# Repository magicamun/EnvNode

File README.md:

# EnvNode

EnvNode is an source-available ESP32-based embedded platform for reliable environmental measurements and seamless integration into modern home automation systems.

WeatherStation is the first reference application built on the reusable EnvNode platform.

The classic ESP32 firmware keeps Arduino-ESP32 2.x and RainDetector, with UDP
logging to rsyslog instead of SD storage. SD and SX1262 runtime support belong
to the later S3 hardware/build profile. See the [classic ESP32 scope](docs/ClassicEsp32Scope.md)
and [logging validation](docs/UdpLoggingValidation.md) for current limits and measurements.

The project intentionally separates **measurement** from **interpretation**.

The firmware is responsible for acquiring reliable physical Measurements and publishing them to external systems.

Higher-level concepts such as weather interpretation, historical aggregation, evapotranspiration (ETo), irrigation logic and visualization intentionally remain outside the firmware.

EnvNode is developed as a complete source-available product including:

- firmware
- hardware (KiCad)
- documentation
- development tooling

The goal is not to build another weather dashboard.

The goal is to build a reliable measurement platform.

---

# Vision

EnvNode provides an open, transparent and extensible weather sensor platform for Home Assistant and other home automation systems.

The ESP32 acts as a dedicated measurement node.

It acquires physical sensor data, performs only the hardware-related processing required to obtain reliable Measurements and publishes them via MQTT.

The firmware intentionally remains deterministic, maintainable and independent from weather-specific interpretation.

This allows higher software layers to evolve independently while keeping the embedded firmware simple and robust.

---

# Why another weather station?

The project originated from practical experience with an existing DIY weather station.

Although the hardware proved to be reliable, several software aspects became increasingly problematic:

- closed-source firmware
- undocumented algorithms
- incorrect sunshine duration calculation
- embedded rain aggregation
- limited extensibility
- unclear separation between measurement and interpretation

Rather than replacing individual algorithms, the firmware was redesigned from first principles around a small number of architectural rules.

---

# Core Philosophy

The EnvNode project follows one simple principle:

> Measure first.
>
> Interpret later.

The firmware exists to acquire reliable Measurements.

Interpretation belongs to external systems.

---

# Project Goals

- source-available firmware with a commercial exploitation reservation
- available hardware design sources (KiCad)
- MQTT-based integration
- browser-based configuration
- OTA firmware updates
- modular architecture
- high-quality Measurements
- deterministic firmware behaviour
- long-term maintainability
- simulation support
- comprehensive documentation
- hardware independence

---

# Design Principles

The project follows a small number of architectural principles.

### Measure, don't interpret

The firmware measures physical reality.

Interpretation belongs outside the Device.

---

### One technical responsibility per service

Each infrastructure service owns exactly one technical responsibility.

Examples include:

- Configuration
- WiFi
- Time
- MQTT

---

### Sensors produce Measurements

Sensors do not publish MQTT.

Sensors do not interpret weather.

Sensors produce Measurements.

### Controllers coordinate Actuators through capabilities

Controllers implement cooperative local behavior and address configured Actuators by `ActuatorId` and capability. They do not manipulate GPIO or use MQTT as an internal control path.

---

### Configuration has one authoritative owner

Configuration exists exactly once inside the runtime.

Every subsystem uses the same Configuration.

---

### Simulation is part of the architecture

Simulated and physical Sensors follow the same processing pipeline.

Replacing a simulated Sensor with a physical implementation must not require architectural changes.

---

### Observable behaviour

Whenever practical, internal decisions should be visible through:

- diagnostics
- logging
- MQTT status

The firmware should never behave like a black box.

---

### Deterministic firmware

The firmware intentionally avoids executing complex weather models.

Embedded software should remain predictable and responsive.

---

### Hardware independence

Application logic depends on abstract Sensor behaviour rather than concrete hardware implementations.

Replacing a Sensor should require only a new driver.

---

# Current Status

Implemented

- ESP32 PlatformIO project
- persistent configuration
- browser-based provisioning
- WiFi connectivity
- automatic WiFi reconnect
- setup access point
- configurable hostname
- SNTP time synchronization
- configurable timezone
- MQTT connectivity
- authenticated MQTT client
- factory reset and OTA firmware update
- typed Measurement pipeline and MQTT publication
- fixed Sensor slots, physical/simulated implementations and live runtime composition
- Sensor Home Assistant discovery
- optional GeoPosition and actual sensor altitude, persisted with backup/restore
- separate sea-level pressure with local temperature selection, freshness checking,
  explicit quality and fallback diagnostics (firmware 0.6.0)
- EEPROM-backed Board Identity, boot-time profile resolution and development fallback
- Board Identity diagnostics and confirmed Web provisioning with readback verification
- independent Module Identity discovery for both slots, immutable module profiles and
  board/slot compatibility diagnostics without automatic driver activation
- fixed Actuator slots and unified hardware validation
- OnOff capability and GPIO On/Off Actuator
- Level capability and GPIO PWM Actuator
- live Actuator runtime rebuild
- Web and MQTT Actuator configuration/control
- fixed Controller slots and BlinkController
- ThresholdController with typed Measurement input, hysteresis and monotonic freshness
- cooperative Controller runtime and live rebuild
- Web and MQTT Controller configuration, status and Start/Stop
- persistent MQTT Blink/Threshold parameter commands and retained parameter state
- retained external Actuator and Controller descriptions
- exclusive enabled-Controller ownership of Actuator targets
- physically verified Sensor -> Measurement -> Controller -> Actuator operation

Current hardware-validation focus

- provision and boot from the Board Identity EEPROM on a physical Mainboard revision 0.3
- complete the Revision 0.3 article list and assembly data
- assemble and bring up the AnalogHydroPressure module, including its local 5 V to 24 V supply
- integrate and calibrate the ADS1115-based 4–20 mA pressure input on real hardware
- operate at least the Rain Detector heater path before releasing Revision 0.3 for production

Deliberately future

- additional Actuator capabilities beyond OnOff and Level, and additional typed Controller implementations
- multi-input, Boolean/contact and event-driven Controllers
- richer manual-versus-Controller arbitration
- Controller and generic Actuator Home Assistant discovery
- a dedicated provisioning station for preparing Mainboards, Modules, and other supported boards

---

# Documentation

Project documentation is intentionally separated by responsibility.

| Document | Purpose |
|----------|---------|
| README.md | Project overview |
| DomainModel.md | Functional domain concepts |
| TechnicalArchitecture.md | Technical architecture |
| ActuatorModel.md | Actuator capabilities and Controller interaction |
| MQTT.md | Current MQTT protocol boundaries and topics |
| Configuration.md | Configuration backup, restore and NVS persistence |
| [SeaLevelPressure.md](docs/SeaLevelPressure.md) | GeoPosition, local temperature input and derived sea-level pressure |
| Hardware.md | Hardware entry point, module templates, and implemented boards |
| [PRODUCT_ASSET_CONTRACT.md](docs/PRODUCT_ASSET_CONTRACT.md) | Reproducible PCB and webshop image requirements |
| ADRs | Architectural decisions |

---

# Non Goals

EnvNode intentionally does not:

- perform weather forecasting
- calculate evapotranspiration (ETo)
- calculate sunshine duration
- aggregate historical weather data
- store long-term measurements
- replace Home Assistant

These responsibilities belong to higher software layers.

---

# Project Status

The Sensor, Actuator and Controller architecture is implemented and physically verified. Current open work concerns further capabilities, Controller implementations and external self-description rather than replacing these runtime boundaries.

# License and permitted use

EnvNode-owned materials are provided under the [EnvNode Use and Redistribution
License, version 1.0](LICENSE). Private and internal business use, modifications,
free redistribution, and paid fabrication or maintenance for the user's own use
are permitted. Commercial product sales, licensing, rental, and standalone paid
software hosting require separate permission. Third-party materials retain their
respective licenses. This is a custom source-available license, not an
OSI-approved open-source license. The German license text is authoritative.

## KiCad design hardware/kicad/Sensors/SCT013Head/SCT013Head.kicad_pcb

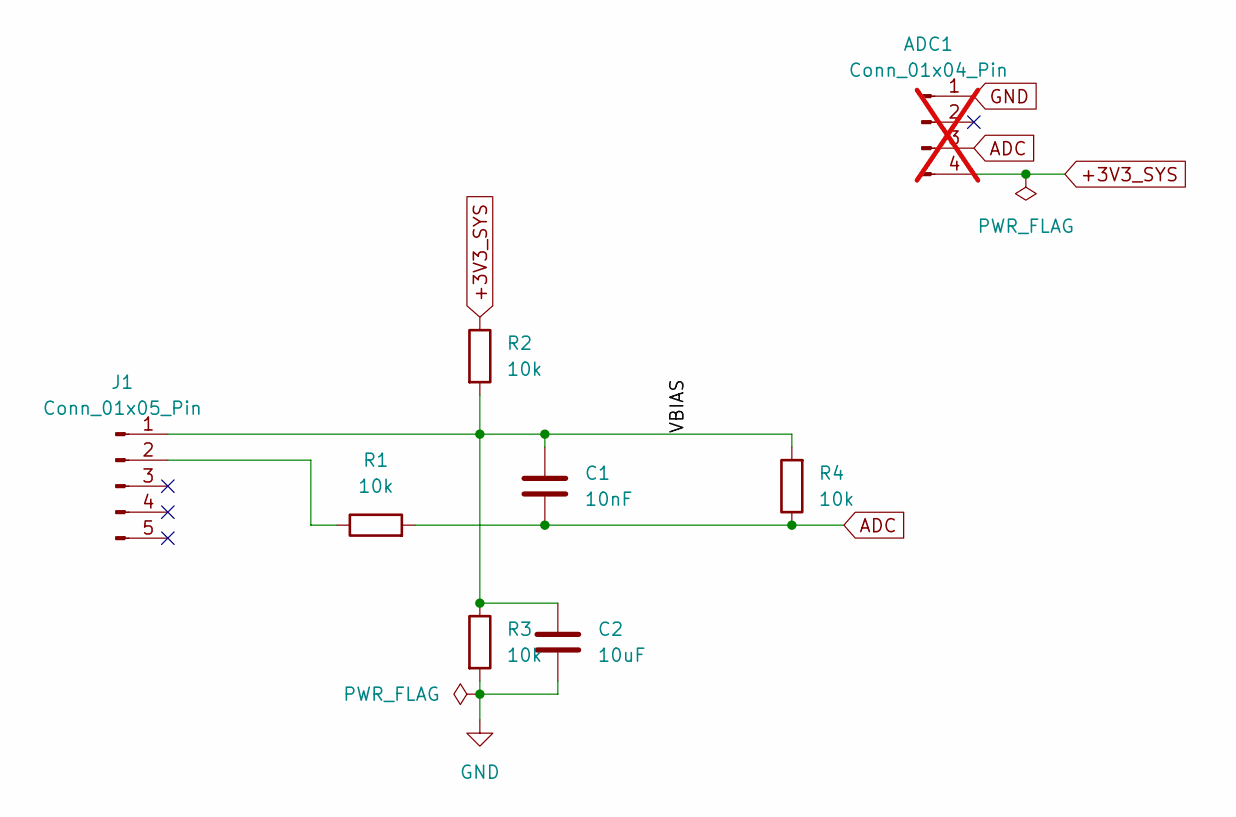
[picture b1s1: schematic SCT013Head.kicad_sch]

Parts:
ADC1: Conn_01x04_Pin; PinHeader_1x04_P2.54mm_Vertical; not fitted
C1: 10nF; C_1206_3216Metric_Pad1.33x1.80mm_HandSolder
C2: 10uF; C_1206_3216Metric_Pad1.33x1.80mm_HandSolder
J1: Conn_01x05_Pin; Jack_3.5mm_Lumberg_1503_09_Horizontal
R1, R2, R3, R4: 10k; R_1206_3216Metric_Pad1.30x1.75mm_HandSolder

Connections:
+3V3_SYS: ADC1.4, R2.1
/VBIAS: C1.1, C2.1, J1.1, R2.2, R3.1, R4.2
ADC: ADC1.3, C1.2, R1.2, R4.1
GND: ADC1.1, C2.2, R3.2
unnamed: J1.2, R1.1

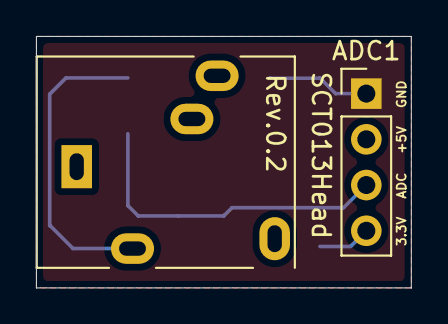
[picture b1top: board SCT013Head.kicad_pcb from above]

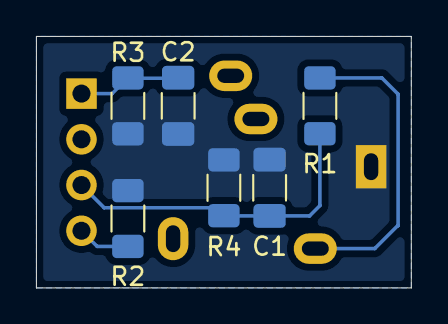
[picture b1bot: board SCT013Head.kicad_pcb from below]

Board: 2 copper layers, 20.8 x 14.0 mm, 8 parts (6 on the bottom side), 5 nets.

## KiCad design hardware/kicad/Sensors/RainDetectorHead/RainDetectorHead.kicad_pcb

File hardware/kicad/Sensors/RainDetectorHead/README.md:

# EnvNode RainDetector Head — Revision 0.2

## Current mechanical revision - 2026-10-21

PCB **ENP-00139**, revision **0.2**, paired with RainDetectorController **0.4**.
The outline is **62.12 x 54.52 mm** (Edge.Cuts centerline), enlarged for the
housing seal; mounting holes moved with the outline. The active C1 detector
geometry, J1/J2 positions/orientations and PCB pad-net assignments are unchanged
relative to the previous committed PCB. No electrical or firmware change follows
from this mechanical revision. The head C1 footprint identifier is
`RainDetector_Interdigitated_44.78x37.25mm_P0.51mm`.

Current guide: [Revision 0.2 assembly and bring-up](Documentation/RainDetectorHead_Bestueckungs_und_Bringup_Rev0.2.pdf).
Structure, typography, ochre colors and component-table columns follow the
DuoRelay revision 0.3 assembly guide.
Native KiCad renders and source fingerprints: [render provenance](../../../../images/rain-detector/README.md).
The guide uses the new PCB article; kit/assembly records are awaiting the user's
update and were not modified here. Prior PDFs and the historical notes below
remain records of their respective revisions, not the current mechanical guide.
No new full ERC/DRC or physical qualification is claimed for the enlarged boards.

## Previous revision notes (historical)

Passive capacitive sensor head with two soldermask-covered interdigitated
F.Cu electrodes and twenty 15-ohm 1206 heater resistors on B.Cu.
The five parallel strings of four resistors give 12 ohms, approximately
417 mA and 2.08 W at 5 V (0.104 W per resistor). Select resistors rated at
least 0.25 W and check their temperature derating.

The controller and head are separate fabrication projects with independent
revisions. This head is paired with RainDetectorController revision 0.3.
The old `../Raindetector/` project is the earlier Stall.biz adapter prototype.

## Interface

| Head contact | Function | Controller contact, nominal assembly |
|---|---|---|
| J1.1 | HEATER+ | J1.1 |
| J1.4 | GND / electrode 2 | J1.4 |
| J2.1 | SENSE / electrode 1 | J2.1 |
| J2.4 | HEATER- | J2.4 |
| J1/J2 pins 2 and 3 | Unconnected, mechanical support | Unconnected |

Both boards face B.Cu toward each other. The SMD header contact axes, not
its alternating solder-pad centers, determine the mating positions.
The current connectors are 2x2 SMD headers. The table lists electrical
assignments from the current PCB, not a mechanical mating qualification.
Verify contact alignment and orientation with the selected sockets before assembly.
Confirm the actual header/socket mating height from the selected parts.

## Sensor and fabrication

C1 represents manufactured copper, not a component to purchase or solder.
The project-local footprint table resolves the sensor footprint from
`../../Libraries/EnvNode-Footprints.pretty`.
The custom design rule permits 0.10 mm clearance only between objects of C1;
other copper keeps its normal clearance requirements.

The sensor pads have no F.Mask or F.Paste openings. The current two vias
are front-plugged and front-tented (Type IV-a intent), NOT filled and capped:
`capping` and `filling` are disabled. Confirm the plugging process and
water exclusion with the fabricator; mask tenting alone is not a seal guarantee.
Any change to Type VII needs explicit fabrication settings and ordering notes.
The nominal 37.25 mm sensor height excludes the connection lobes; including
those, the copper height is about 40.27 mm.

Four 3.2 mm non-plated mounting holes are provided. Confirm screw/washer
clearance, mounting insulation and assembled spacing before manufacture.

## Validation

See `../RainDetectorController/README.md` for the shared validation commands.
ERC/DRC are design checks, not hardware or environmental qualification.
The assembled coated head has not yet been manufactured or tested.

Documentation correction, 2026-10-05: J2.1 is SENSE and J2.4 is HEATER- in the current PCB; the previous table described the earlier connector arrangement. The current outline is 62.12 x 44.12 mm. Historical 2026-09-14 checks predate the connector/outline changes committed on 2026-09-15.

## Assembly guide — 2026-10-06

`Documentation/RainDetectorHead_Bestueckungs_und_Bringup_Rev0.1.pdf` documents the current 62.12 x 44.12 mm board, 2x2 SMD headers, heater assembly, controller contact mapping, fabrication requirements, and separate heater/sensor checks. It includes current source hashes and PCB views using the common ORing camera angles.

The exported schematic netlist and PCB pad nets match. The heater was verified as five parallel strings of four 15-ohm resistors (R1-R4, R5-R8, R9-R12, R13-R16, R17-R20). No new full ERC/DRC or physical testing was performed for this documentation update.

Assembly table update, 2026-10-17: PDF page 2 now lists kit ENK-00005 and the
EnvNode article numbers, quantities and packages from `inventory/assemblies.rain.draft.json`
and `inventory/parts-preview.json`. ENP-00111 is one complete 2x10 strip for two
2x2 cut pieces. C1, mounting holes and separately required mounting hardware are
distinguished from purchased kit components. Other PDF pages remain unchanged.

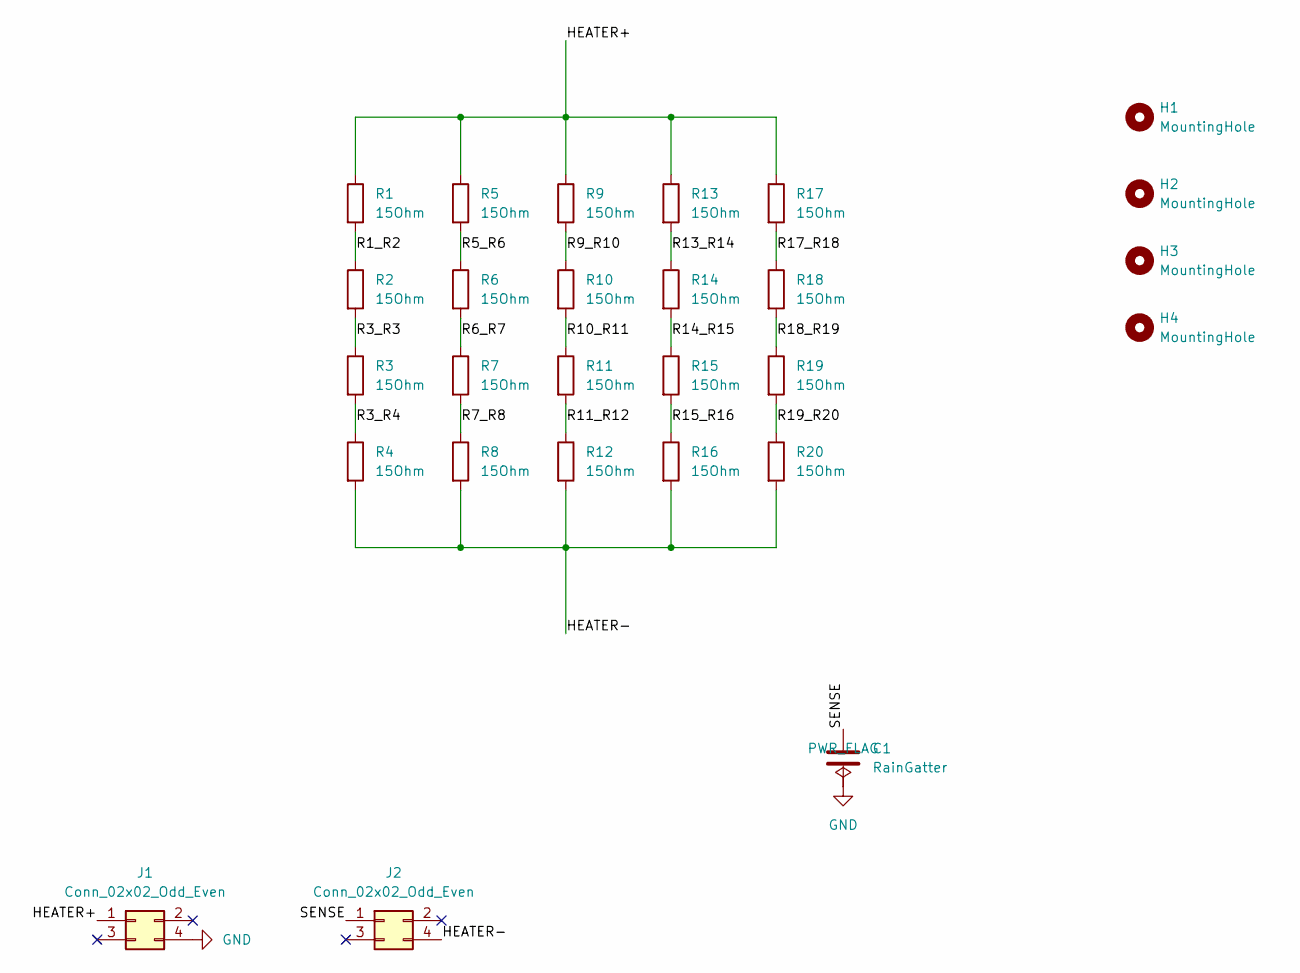
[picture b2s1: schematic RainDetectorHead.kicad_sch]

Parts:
C1: RainGatter; RainDetector_Interdigitated_44.78x37.25mm_P0.51mm
H1, H2, H3, H4: MountingHole; MountingHole_3.2mm_M3
J1, J2: Conn_02x02_Odd_Even; PinHeader_2x02_P2.54mm_Vertical_SMD
R1, R2, R3, R4, R5, R6, R7, R8, R9, R10, R11, R12, R13, R14, R15, R16, R17, R18, R19, R20: 15Ohm; R_1206_3216Metric_Pad1.30x1.75mm_HandSolder

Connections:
/HEATER+: J1.1, R1.1, R5.1, R9.1, R13.1, R17.1
/HEATER-: J2.4, R4.2, R8.2, R12.2, R16.2, R20.2
/R1_R2: R1.2, R2.1
/R3_R3: R2.2, R3.1
/R3_R4: R3.2, R4.1
/R5_R6: R5.2, R6.1
/R6_R7: R6.2, R7.1
/R7_R8: R7.2, R8.1
/R9_R10: R9.2, R10.1
/R10_R11: R10.2, R11.1
/R11_R12: R11.2, R12.1
/R13_R14: R13.2, R14.1
/R14_R15: R14.2, R15.1
/R15_R16: R15.2, R16.1
/R17_R18: R17.2, R18.1
/R18_R19: R18.2, R19.1
/R19_R20: R19.2, R20.1
/SENSE: C1.1, J2.1
GND: C1.2, J1.4

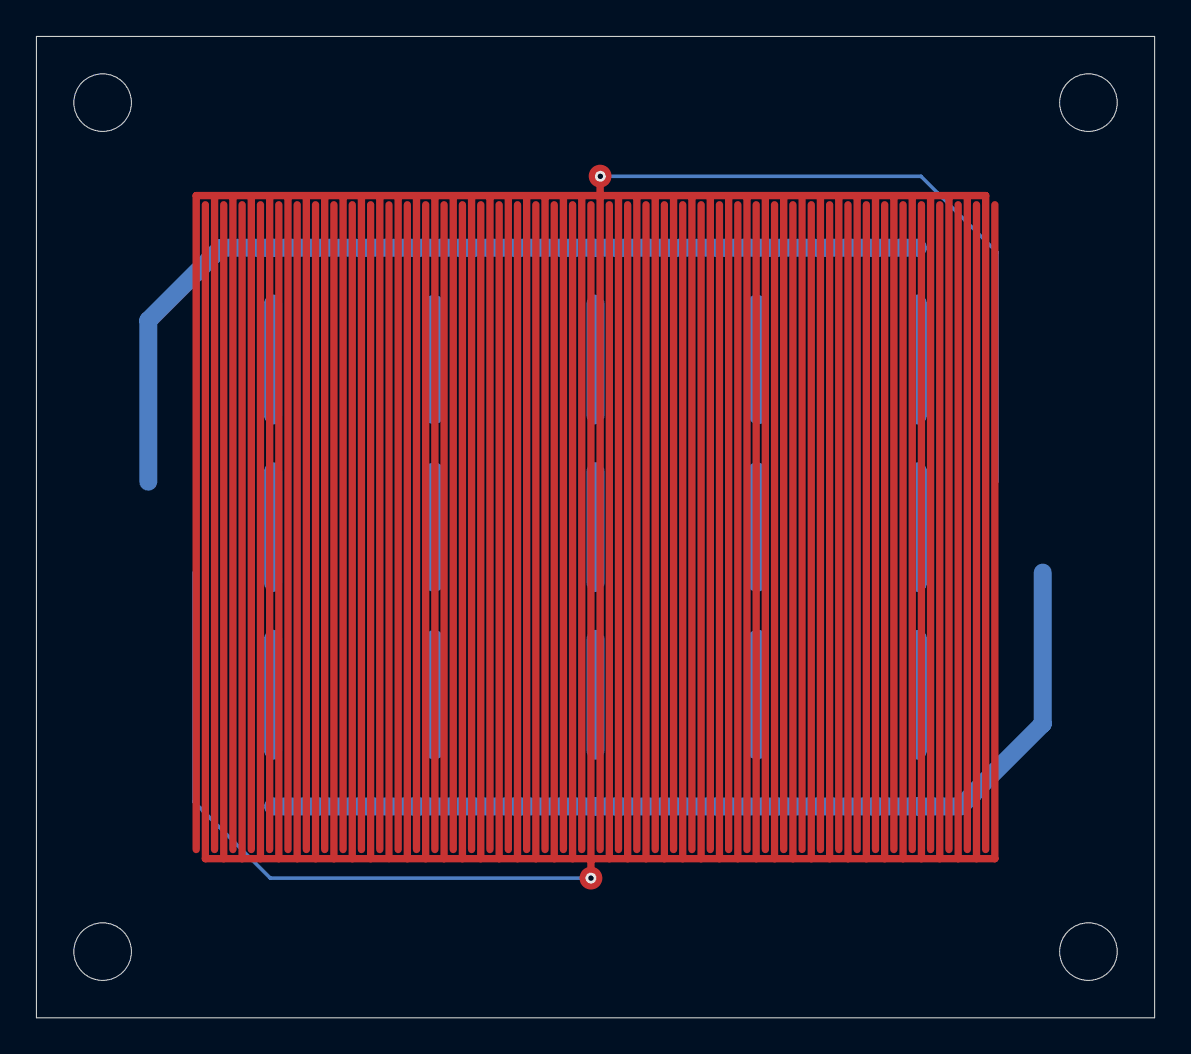
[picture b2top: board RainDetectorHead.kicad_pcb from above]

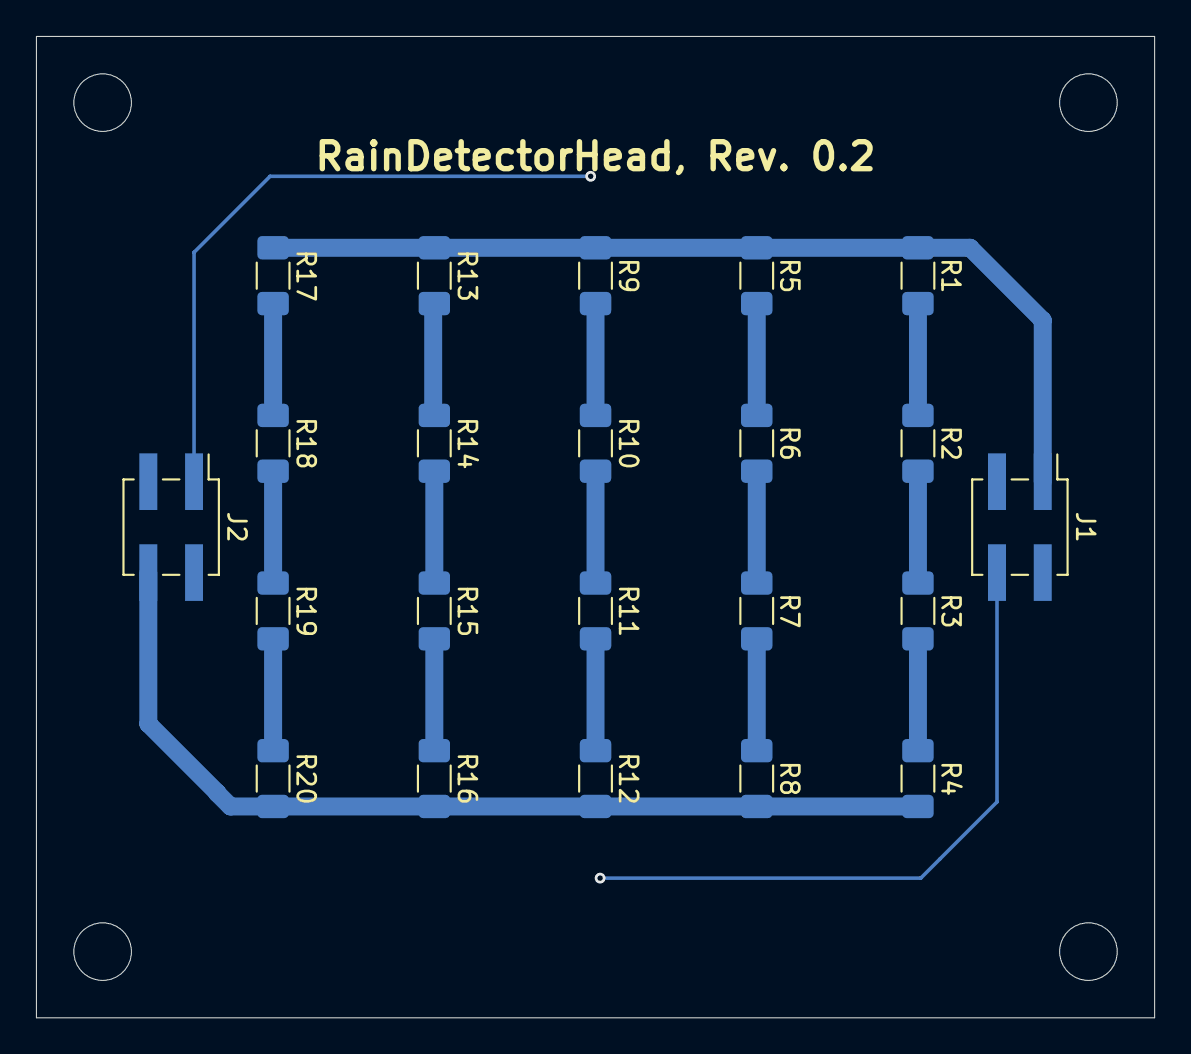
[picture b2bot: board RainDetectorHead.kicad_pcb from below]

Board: 2 copper layers, 62.1 x 54.5 mm, 27 parts (22 on the bottom side), 19 nets.

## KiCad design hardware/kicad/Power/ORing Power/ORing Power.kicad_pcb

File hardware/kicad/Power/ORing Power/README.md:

# ORing Power Module

The ORing Power module is a 39 mm x 15 mm castellated daughterboard for EnvNode mainboards. It combines the external 5 V input, the 3.3 V regulator, and the diode ORing between the regulator output and the ESP32 DevKit 3.3 V rail. Mainboards use the matching carrier footprint and no longer need to reproduce this circuit locally.

## Project and Library Items

- Editable KiCad project: `hardware/kicad/Power/ORing Power/`
- Published design block: `hardware/kicad/Libraries/EnvNodeDesignBlocks.kicad_blocks/ORing Power.kicad_block/`
- Mainboard symbol: `EnvNode-Symbols:ORingPower_Module`
- Module footprint: `EnvNode-Footprints:ORingPower_Module_Castellated`
- Mainboard carrier footprint: `EnvNode-Footprints:ORingPower_Carrier`
- Assembly and bring-up guide: `Documentation/ORing_Power_Bestueckungs_und_Bringup_Rev0.1.pdf`

The symbol defaults to the carrier footprint. The ORing Power PCB itself overrides that assignment with the module-side castellated footprint.

## Electrical Function

The module accepts 5 V through either the two-pin JST-PH connector or the USB-C connector. These two 5 V inputs share the same `+5V` net and are not isolated from one another. Do not connect independent supplies to both connectors unless they are explicitly suitable for direct parallel operation.

The LM3940 generates `+3V3_EXT` from `+5V`. Two SS14 Schottky diodes combine `+3V3_EXT` and the mainboard-provided `+3V3_DEVKIT` rail into `+3V3_SYS`. The topology prevents either 3.3 V source from feeding back into the other through the ORing path.

The USB-C connector is the six-contact, power-only GCT `USB4125-GF-A-0190`. `CC1` and `CC2` each have their own 5.1 kΩ pull-down resistor to GND. The connector does not expose USB data signals and does not implement USB Power Delivery negotiation; it requests the standard USB-C 5 V source mode only.

## Castellated Interface

| Pin | Net | Module direction | Function |
| ---: | --- | --- | --- |
| 1 | `GND` | Common | Ground |
| 2 | `+5V` | Output to mainboard | Shared 5 V input rail |
| 3 | `+3V3_EXT` | Output to mainboard | LM3940 regulator output before ORing diode |
| 4 | `+3V3_DEVKIT` | Input from mainboard | ESP32 DevKit 3.3 V source before ORing diode |
| 5 | `+3V3_SYS` | Output to mainboard | ORed system 3.3 V rail |

Pin numbers, net names, pad positions, and module orientation are contractual. A carrier PCB must use the matching carrier footprint without moving individual pads.

## Mechanical Integration

The module is soldered directly onto the mainboard using the five castellated edge pads. The carrier footprint reserves the 39 mm x 15 mm module outline and provides matching mainboard pads. Before releasing a mainboard, verify:

- the module outline and nearby component courtyards do not overlap;
- the USB-C opening is reachable at the intended enclosure edge;
- sufficient solder fillet is accessible at every castellated pad;
- no mainboard copper, vias, or components occupy the reserved module area; and
- the assembly process supports castellated-hole soldering on the selected PCB finish and thickness.

The castellated-hole geometry must be confirmed with the PCB manufacturer before the first production order. Fabrication outputs must identify the edge-plated half holes correctly; ordinary routed holes without edge plating are not an equivalent substitute.

## Component Notes

| Reference | Function | Important assignment |
| --- | --- | --- |
| J3 | USB-C 5 V input | GCT `USB4125-GF-A-0190`; KiCad six-pin power-only footprint |
| R1, R2 | USB-C Rd | 5.1 kΩ each, one resistor per CC pin |
| J1 | Alternate 5 V input | JST `B2B-PH-SM4-TB`, two-pin, vertical SMD; KiCad footprint `JST_PH_B2B-PH-SM4-TB_1x02-1MP_P2.00mm_Vertical` |
| U1 | 3.3 V regulator | `LM3940IMP-3.3/NOPB`, SOT-223 |
| D1, D2 | 3.3 V source ORing | SS14, SMA |
| C1, C5 | Local bypass | 100 nF, 1206 |
| C2 | System rail bulk capacitor after D1/D2 | 47 µF / 6.3 V, Nichicon `UWG0J470MCL1GB`, `CP_Elec_5x5.4`; polarity required |
| C3 | 5 V input capacitor | 10 µF ceramic, 1206 |
| C4 | Regulator output capacitor before D1 | 47 µF tantalum, EIA-3528-21; polarity required |

## Mainboard Use

1. Place `EnvNode-Symbols:ORingPower_Module` in the mainboard schematic.
2. Keep its default `EnvNode-Footprints:ORingPower_Carrier` footprint.
3. Connect all five named rails according to the interface table.
4. Update the PCB from the schematic and place the complete carrier footprint at the intended board edge.
5. Remove the former discrete ORing-power circuit and verify that no duplicate regulator, diode, USB-C, or input components remain.
6. Run ERC, PCB/schematic parity, DRC, and a visual 3D/mechanical review on the completed mainboard.

Do not place the module-side castellated footprint on the mainboard. Do not use the carrier footprint as the outline of a separately fabricated ORing Power PCB.

## Validation Status

Checked with KiCad 10 on 2026-09-21:

- schematic ERC: 0 errors, 0 warnings;
- PCB DRC: 0 violations and 0 unconnected items;
- all seven electrical nets have zero unrouted connections;
- USB VBUS, GND, shield, CC1, and CC2 map to the expected footprint pads;
- the GCT USB4125 footprint is aligned with the PCB edge; and
- the editable source and published library block are synchronized.

This validation covers design consistency, not physical manufacture. The first fabricated module still requires continuity, polarity, 5 V input, 3.3 V regulation, source handover, reverse-current, thermal, USB-C insertion, and castellated-solder-joint tests.

## Documentation verification — 2026-10-05

The Revision 0.1 assembly guide now carries current PCB, schematic, and parts-workbook hashes. The PCB has no formal title-block revision; 0.1 is the existing documentation designation. Compared with the previously documented PCB, only plot settings, an empty settings block, and serialization order changed; board geometry and circuitry are unchanged. The existing 3D reference view remains valid.

The guide previously swapped the diode references in its functional description and tests: D1 connects `+3V3_EXT` to `+3V3_SYS`, while D2 connects `+3V3_DEVKIT` to `+3V3_SYS`. These references are corrected. PCB pad nets were checked against an exported schematic netlist and matched. This documentation check did not repeat full ERC/DRC or physical testing.

## PCB patch 0.1.1 (18 October 2026)

The PCB now has a formal title block with revision 0.1.1 and front-silkscreen
labels for the module and the two-pin JST-PH 5 V input. J1 pin 1 remains GND;
pin 2 remains +5V. All other PCB data, including copper, pad geometry, components,
board outline and mounting geometry, is identical to the previous committed PCB.
The existing Revision 0.1 assembly guide remains applicable; this patch requires
no mainboard profile change or reprovisioning. See the shared
[PCB patch convention](../../../../docs/BoardIdentityRecord.md).

The 5 October verification above describes the earlier source snapshot. No new
ERC/DRC or physical qualification is claimed by this silkscreen-only update.
The published library design block remains at its earlier snapshot; it has not
been republished with these labels. No new 3D illustration was generated.

## Illustrated edge-pad test points (18 October 2026)

The assembly PDF includes an additional landscape reference page for all five U2
castellated pads, their nets and the standalone-module measurement conditions.
The [web guide](../../../../docs/site/mainboards/oring-power/index.md) contains the
same overview and test-point table. Measurements use U2.1 / GND as their reference.
The native PCB/STEP render omits the unavailable J1 housing model; its actual
footprint remains visible. See [render provenance and sources](../../../../images/oring-power/testpoints/README.md).

## Assembly specification 0.1.2 (8 November 2026)

C2 changes from 10 µF to 47 µF / 6.3 V, Nichicon `UWG0J470MCL1GB`.
The existing `CP_Elec_5x5.4` footprint, signal routing and mounting geometry
remain unchanged. J1 uses the project symbol with its MP mounting pads explicitly
connected to GND; the silkscreen boundary clears these pads. C2 is the system reservoir on `+3V3_SYS` after
D1/D2. C4, already 47 µF tantalum on `+3V3_EXT`, is the actual LM3940
output capacitor. Earlier prose interchanged these functions; the schematic
and PCB connections agree. Increasing C2 is additional system buffering,
not a correction of an allegedly undersized LM3940 output capacitor.

Revision 0.1.2 is the user's explicit assembly-specification exception to the
usual documentation-only PCB patch convention. Existing 0.1.1 bare PCBs can
use this BOM; a populated board needs C2 replacement to match 0.1.2.
The ORing module has no identity EEPROM; mainboard profiles and provisioning
are unaffected. Historical PDFs and render provenance remain at their original
revision. The reusable design block remains the historical snapshot and must
not be used as the 0.1.2 BOM without adopting this C2 substitution.

Sourcing and dimensional verification are recorded in
[C2 procurement](Documentation/C2-procurement-0.1.2.json): DigiKey
`493-9737-1-ND`, cut tape, minimum one piece. This is a separate 47 µF part;
ENP-00056 and its 10 µF stock must not be relabeled. The new InvenTree part is
ENP-00179 (part 200), with Nichicon MPN and DigiKey SKU verified. Physical load-step/temperature validation remains open.

Latest saved-state check: 2026-11-09, KiCad 10.0.5, ERC 0, DRC 0,
no unconnected items or schematic/PCB mismatches. See
[validation record](Documentation/Validation-0.1.2.json). Current product images
are generated separately as `oring-power-0.1.2`; historical guide images retain
their original 0.1.1 provenance.

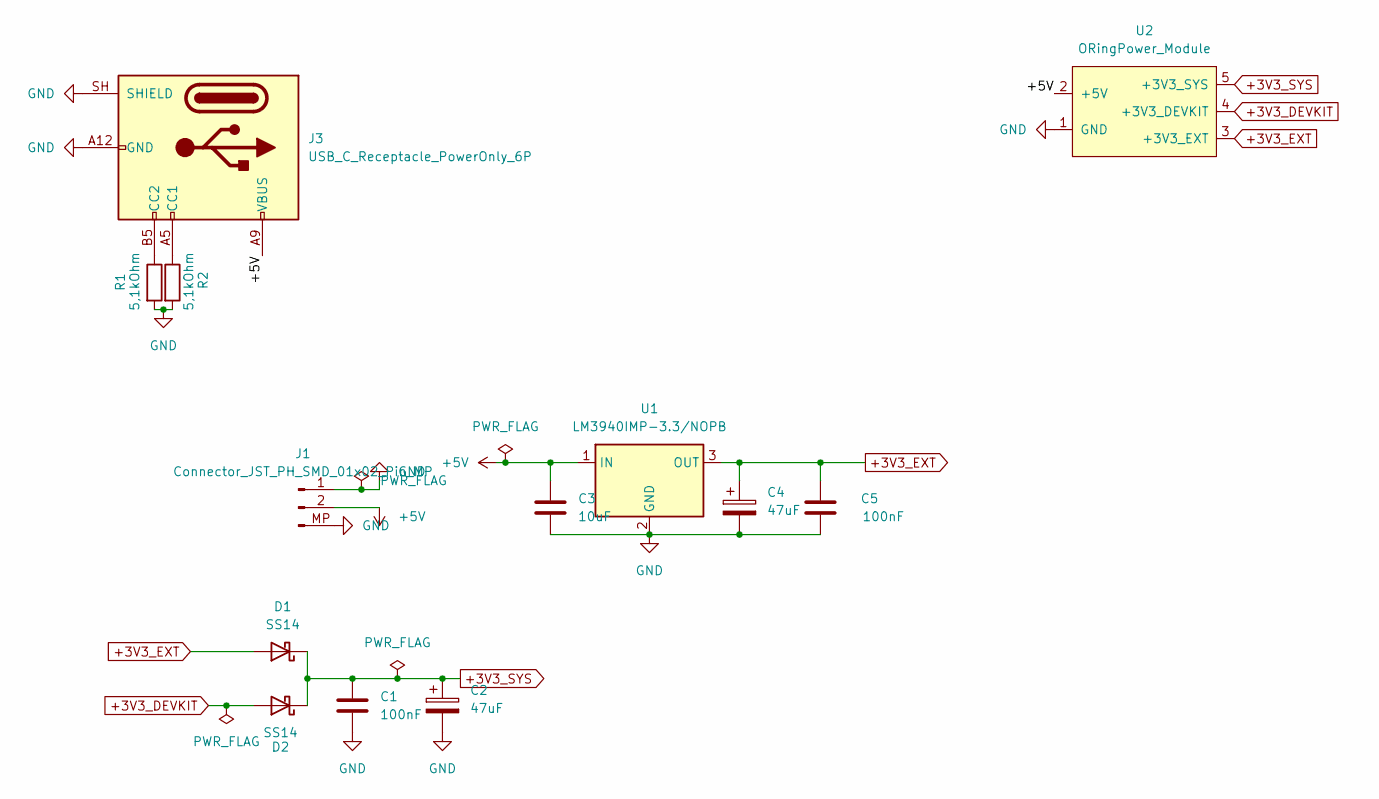
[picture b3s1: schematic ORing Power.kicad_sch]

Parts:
C1, C5: 100nF; C_1206_3216Metric_Pad1.33x1.80mm_HandSolder
C2: 47uF; CP_Elec_5x5.4
C3: 10uF; C_1206_3216Metric_Pad1.33x1.80mm_HandSolder
C4: 47uF; CP_EIA-3528-21_Kemet-B
D1, D2: SS14; D_SMA
J1: Connector_JST_PH_SMD_01x02_Pin_MP; JST_PH_B2B-PH-SM4-TB_1x02-1MP_P2.00mm_Vertical
J3: USB_C_Receptacle_PowerOnly_6P; USB_C_Receptacle_GCT_USB4125-xx-x-0190_6P_TopMnt_Horizontal
R1, R2: 5,1kOhm; R_1206_3216Metric_Pad1.30x1.75mm_HandSolder
U1: LM3940IMP-3.3/NOPB; SOT-223-3_TabPin2
U2: ORingPower_Module; ORingPower_Module_Castellated

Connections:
+3V3_DEVKIT: D2.2 (A), U2.4 (+3V3_DEVKIT)
+3V3_EXT: C4.1, C5.2, D1.2 (A), U1.3 (OUT), U2.3 (+3V3_EXT)
+3V3_SYS: C1.1, C2.1, D1.1 (K), D2.1 (K), U2.5 (+3V3_SYS)
+5V: C3.1, J1.2, J3.A9 (VBUS), J3.B9 (VBUS), U1.1 (IN), U2.2 (+5V)
GND: C1.2, C2.2, C3.2, C4.2, C5.1, J1.1, J1.MP (Pin_3), J3.A12 (GND), J3.B12 (GND), J3.SH (SHIELD), R1.2, R2.2, U1.2 (GND), U2.1 (GND)
unnamed: J3.A5 (CC1), R2.1
unnamed: J3.B5 (CC2), R1.1

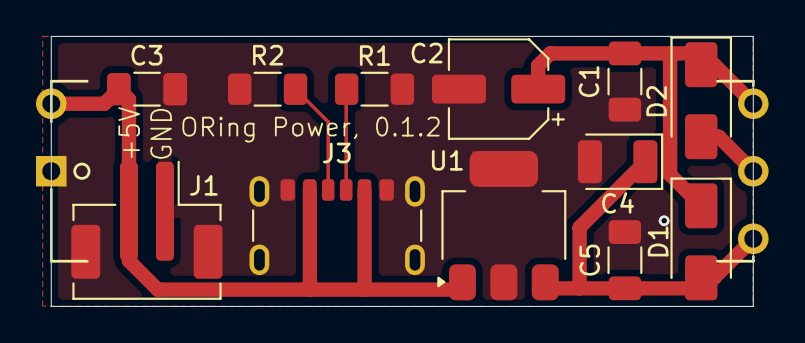
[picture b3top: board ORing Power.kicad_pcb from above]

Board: 2 copper layers, 39.0 x 15.0 mm, 13 parts (0 on the bottom side), 7 nets.

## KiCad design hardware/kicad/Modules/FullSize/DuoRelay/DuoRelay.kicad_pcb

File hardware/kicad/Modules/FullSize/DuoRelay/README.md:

# EnvNode DuoRelay

`DuoRelay` is a FullSize THT daughterboard for the EnvNode Revision 0.3 module interface. It provides two independently controlled 5 V electromechanical changeover relays.

## Project Files

- `DuoRelay.kicad_pro`
- `DuoRelay.kicad_sch`
- `DuoRelay.kicad_pcb`
- `Documentation/DuoRelay_Bestueckungs_und_Bringup_Rev0.3.pdf` — current assembly and bring-up guide; Revision 0.2 remains historical.

## Interface Use

| Connector pin | Net | DuoRelay use |
| ---: | --- | --- |
| 1 | `GND` | Control-side ground |
| 2 | `+3V3_SYS` | Identification EEPROM supply and fixed `A1` level |
| 3 | `EEPROM_A0` | Slot-defined identification EEPROM address bit |
| 4 | `+5V` | Relay-coil supply |
| 5–6 | `I2C0` | Identification EEPROM |
| 7–8 | `I2C1` | Not used |
| 9 | `AUX_GPIO1` | Relay channel 1 control |
| 10 | `AUX_GPIO2` | Relay channel 2 control |
| 11–14 | SPI | Not used |

Each channel uses a BC817 low-side driver with a 1 kΩ base resistor, a 100 kΩ pull-down for a defined off state, and a 1N4148W flyback diode. An LED with a 1.5 kΩ series resistor is connected from `+5V` to each transistor collector and lights while the corresponding relay is driven. The indication confirms the electrical drive state, not the mechanical position of the relay contacts. The relays are Finder `34.51.7.005.0010` parts with 5 V coils.

## Module Identification

The board provides a `24LC32` (U2, SOIC-8; kit part ENP-00102 / `24LC32A-I/SN`) module-identification EEPROM and a local 100 nF decoupling capacitor (C1) on the bottom side. The EEPROM follows the EnvNode discovery convention:

- SDA and SCL use `I2C0`;
- `A1` is tied to `+3V3_SYS`;
- `A0` uses connector pin 3 / `EEPROM_A0`;
- Slot A therefore selects `0x52`; and
- Slot B selects `0x53`.

During bring-up, verify the 3.3 V supply, I2C0 address and a valid provisioned module descriptor. Firmware discovers the reserved module EEPROM addresses independently for both slots, resolves supported records through the module-profile registry, and reports board/slot compatibility diagnostically. Discovery does not yet create a DuoRelay-specific driver or UI controls automatically. The relay circuitry remains electrically functional without the EEPROM. Without a valid descriptor, firmware cannot identify the module, validate compatibility or derive module-specific settings. Explicit manual configuration and suitable driver support are required. Without a valid identity, firmware treats the relay GPIOs as ordinary configurable `AUX_GPIO` ports and must not automatically start a DuoRelay-specific driver.

## Mechanical Geometry

- PCB: 38.00 mm × 64.00 mm
- Connector: bottom-mounted 2 × 7 THT header
- Connector axis: centered across the board and 6.35 mm from the top edge
- Support holes: 2.7 mm for M2.5 hardware, on the centerline at 27.00 mm and 59.00 mm from the top edge

The sales kit includes one mainboard mounting set: one ENP-00164 M2.5 x 10 mm
spacer, one ENP-00165 M2.5 x 8 mm screw and one ENP-00166 M2.5 nut. These parts
are included in the validated live BOM for ENK-00002.

## Relay Contact Region

The relay-contact nets are routed on F.Cu with 1.0 mm tracks. The design keeps at least 8 mm between the 250 VAC contact region and all SELV copper on both layers, including GND zones, vias, pads, and traces.

The spacing and relay ratings do not by themselves certify the finished product for mains use. Terminal ratings, enclosure, touch protection, fusing, load type, pollution degree, material group, overvoltage category, manufacturing tolerances, and the applicable product standard must be assessed for the final application.

## Validation

Revision 0.3 aligns the bottom-side identification EEPROM, its decoupling capacitor, vias, and connector routing with the FullSize THT module template.

At the time of the Revision 0.2 port:

- schematic ERC reports no errors; its nine warnings comprise six intentionally unused connector nets and three same-name local/global label warnings for `+3V3_SYS`, `I2C0_SDA`, and `I2C0_SCL`;
- PCB DRC reports no violations, unconnected pads, or footprint errors; and
- connector placement, board outline, support-hole positions, power routing, relay drivers, status LEDs, and contact separation were checked against the source design.

ERC and DRC must be repeated after every schematic, footprint, routing, zone, or rule change.

## Documentation verification — 2026-10-05

The Revision 0.3 guide documents U2 (24LC32A-I/SN, SOIC-8) and C1 (100 nF). The bottom view and source checksums were updated from the saved KiCad project on 2026-10-17; the PCB revision remains unchanged. All common component-pin nets in the exported schematic netlist and PCB were compared and matched, including relay contacts and EEPROM address wiring. The bottom view shows U2 and C1 populated. No new full ERC/DRC run or physical validation was performed; the historical Revision 0.2 validation above is not a release check for Revision 0.3.

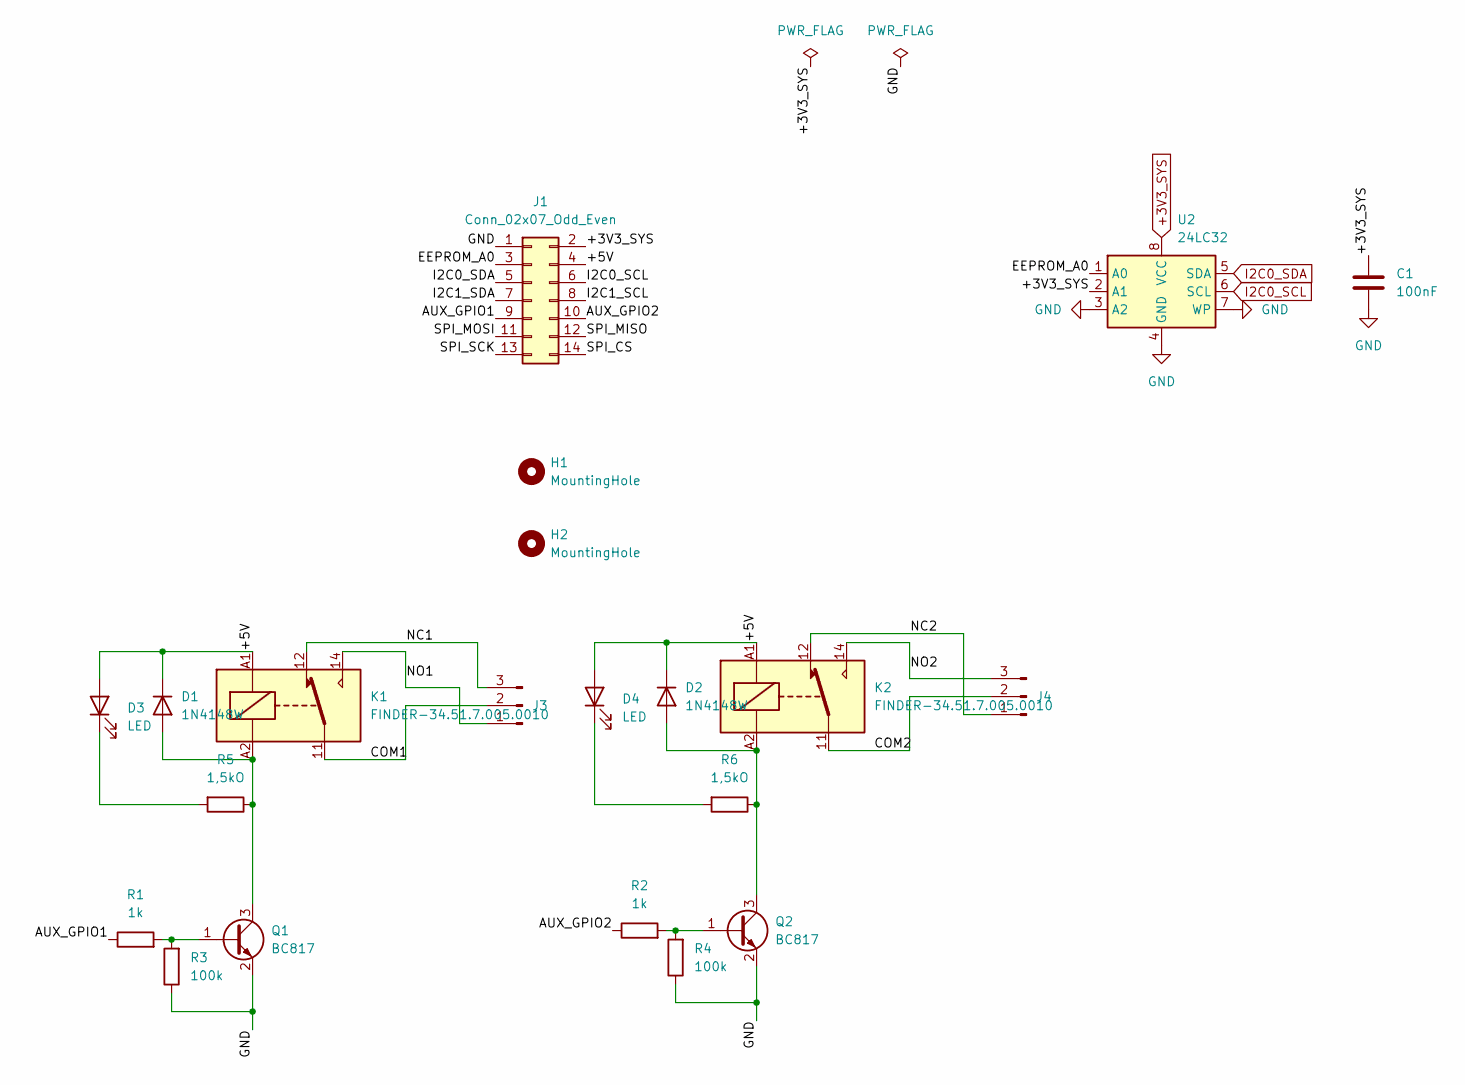
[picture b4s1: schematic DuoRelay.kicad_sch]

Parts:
C1: 100nF; C_1206_3216Metric_Pad1.33x1.80mm_HandSolder
D1, D2: 1N4148W; D_SOD-123
D3, D4: LED; LED_1206_3216Metric_Pad1.42x1.75mm_HandSolder
H1, H2: MountingHole; MountingHole_2.7mm_M2.5_DIN965
J1: Conn_02x07_Odd_Even; PinHeader_2x07_P2.54mm_Vertical_Bottom
J3, J4: TerminalBlock_Phoenix_MKDS-3-3-5.08_1x03_P5.08mm_Horizontal
K1, K2: FINDER-34.51.7.005.0010; Relay_SPDT_Finder_34.51_Vertical
Q1, Q2: BC817; SOT-23_Handsoldering
R1, R2: 1k; R_1206_3216Metric_Pad1.30x1.75mm_HandSolder
R3, R4: 100k; R_1206_3216Metric_Pad1.30x1.75mm_HandSolder
R5, R6: 1,5kO; R_1206_3216Metric_Pad1.30x1.75mm_HandSolder
U2: 24LC32; SOIC-8_3.9x4.9mm_P1.27mm

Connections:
+3V3_SYS: C1.1, J1.2, U2.2 (A1), U2.8 (VCC)
/+5V: D1.1 (K), D2.1 (K), D3.2 (A), D4.2 (A), J1.4, K1.A1, K2.A1
/AUX_GPIO1: J1.9, R1.1
/AUX_GPIO2: J1.10, R2.1
/COM1: J3.2, K1.11
/COM2: J4.2, K2.11
/EEPROM_A0: J1.3, U2.1 (A0)
/I2C1_SCL: J1.8
/I2C1_SDA: J1.7
/NC1: J3.3, K1.12
/NC2: J4.1, K2.12
/NO1: J3.1, K1.14
/NO2: J4.3, K2.14
/SPI_CS: J1.14
/SPI_MISO: J1.12
/SPI_MOSI: J1.11
/SPI_SCK: J1.13
GND: C1.2, J1.1, Q1.2 (E), Q2.2 (E), R3.1, R4.1, U2.3 (A2), U2.4 (GND), U2.7 (WP)
I2C0_SCL: J1.6, U2.6 (SCL)
I2C0_SDA: J1.5, U2.5 (SDA)
unnamed: D1.2 (A), K1.A2, Q1.3 (C), R5.1
unnamed: D2.2 (A), K2.A2, Q2.3 (C), R6.1
unnamed: D3.1 (K), R5.2
unnamed: D4.1 (K), R6.2
unnamed: Q1.1 (B), R1.2, R3.2
unnamed: Q2.1 (B), R2.2, R4.2

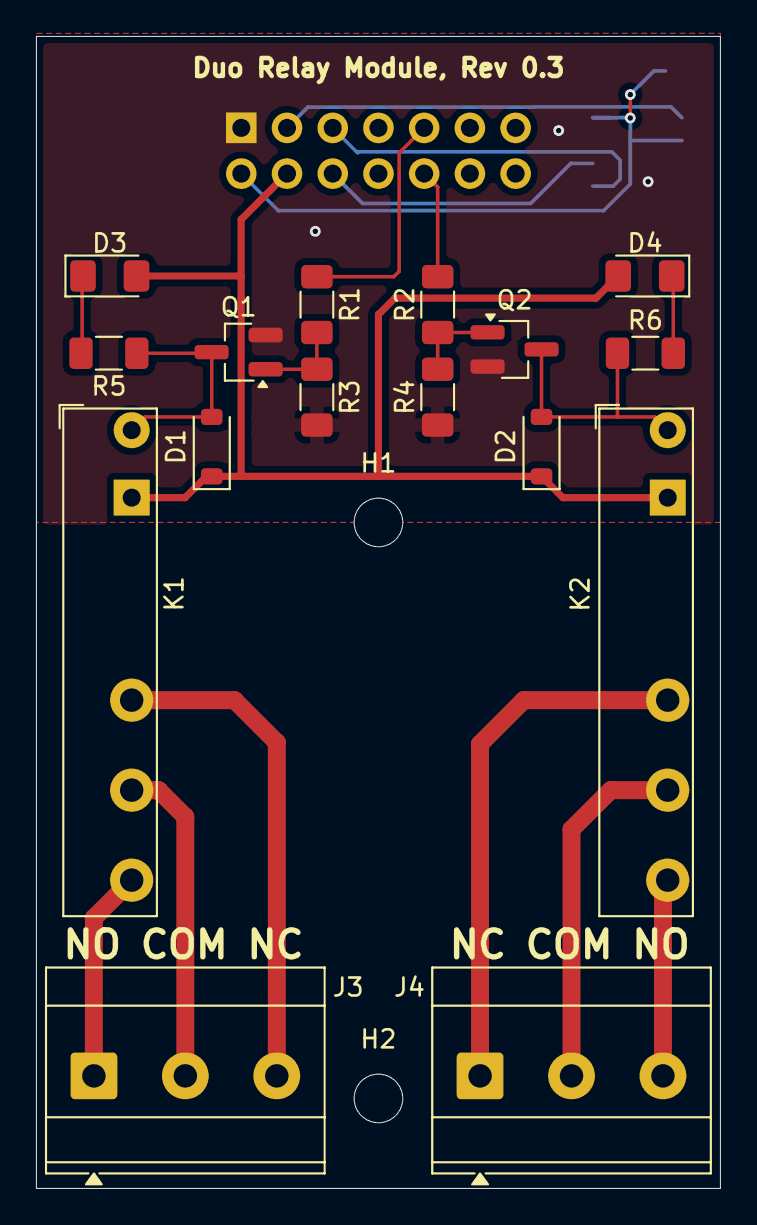
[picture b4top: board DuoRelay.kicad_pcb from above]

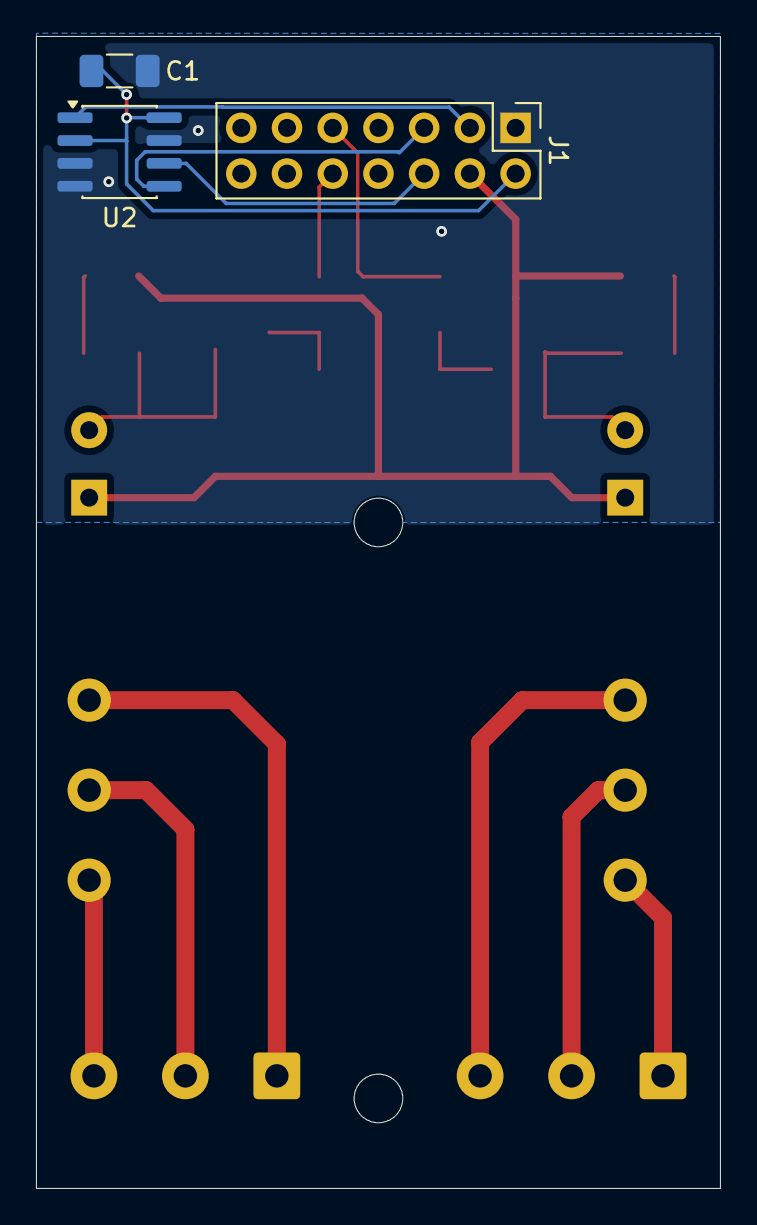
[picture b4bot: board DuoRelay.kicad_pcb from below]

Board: 2 copper layers, 38.0 x 64.0 mm, 21 parts (3 on the bottom side), 20 nets.

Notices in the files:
parts and their libraries:
Adafruit product 254, top-mounted breakout on vertical 1x08 2.54 mm header; CC-BY-SA-3.0, see ../Adafruit-Breakouts/LICENSE.txt
Adafruit 254 microSD breakout; CC-BY-SA-3.0, see Adafruit-Breakouts/LICENSE.txt
